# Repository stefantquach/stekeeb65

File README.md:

# stekeeb65

## Libraries
https://github.com/ai03-2725/MX_V2

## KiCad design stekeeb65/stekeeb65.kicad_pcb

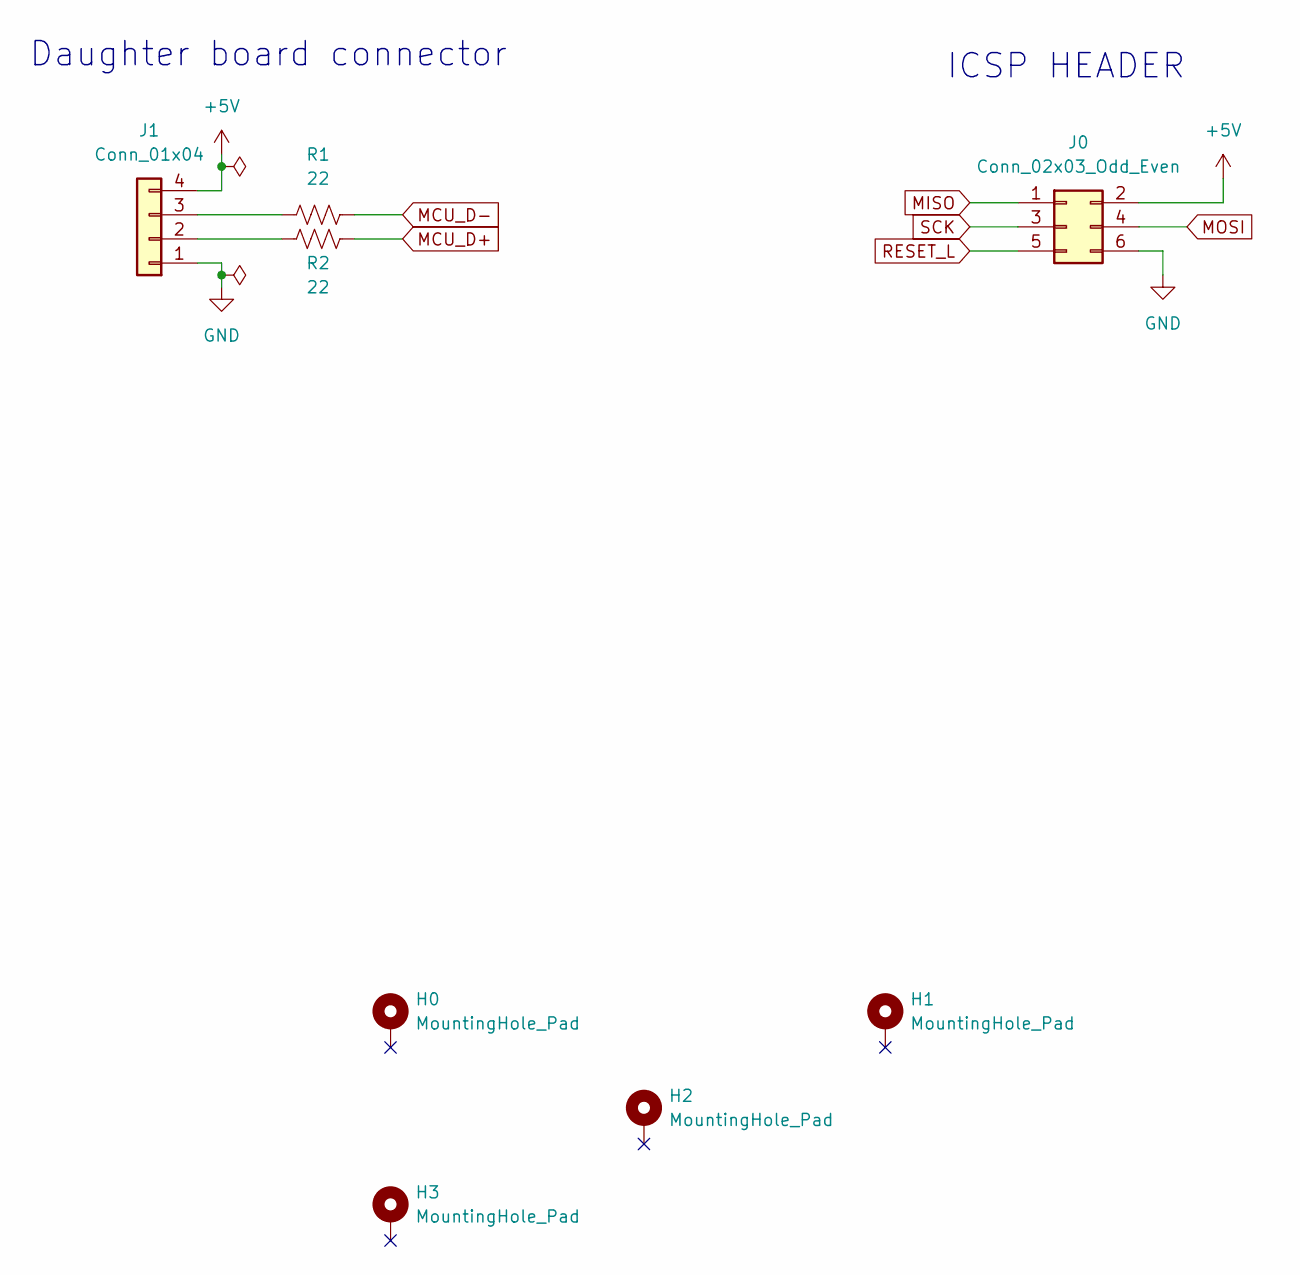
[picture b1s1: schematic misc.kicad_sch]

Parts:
H0, H1, H2, H3: MountingHole_Pad; MountingHole_2.2mm_M2_DIN965_Pad_TopBottom
J0: Conn_02x03_Odd_Even; PinHeader_2x03_P2.54mm_Vertical
J1: Conn_01x04; JST_SH_SM04B-SRSS-TB_1x04-1MP_P1.00mm_Horizontal
R1, R2: 22; R_0603_1608Metric_Pad0.98x0.95mm_HandSolder

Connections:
+5V: J0.2, J1.4; also elsewhere on the board
GND: J0.6, J1.1; also elsewhere on the board
MCU_D+: R2.1; also elsewhere on the board
MCU_D-: R1.2; also elsewhere on the board
MISO: J0.1; also elsewhere on the board
MOSI: J0.4; also elsewhere on the board
unnamed: J1.2, R2.2
unnamed: J1.3, R1.1
RESET_L: J0.5; also elsewhere on the board
SCK: J0.3; also elsewhere on the board

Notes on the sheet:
ICSP HEADER
Daughter board connector

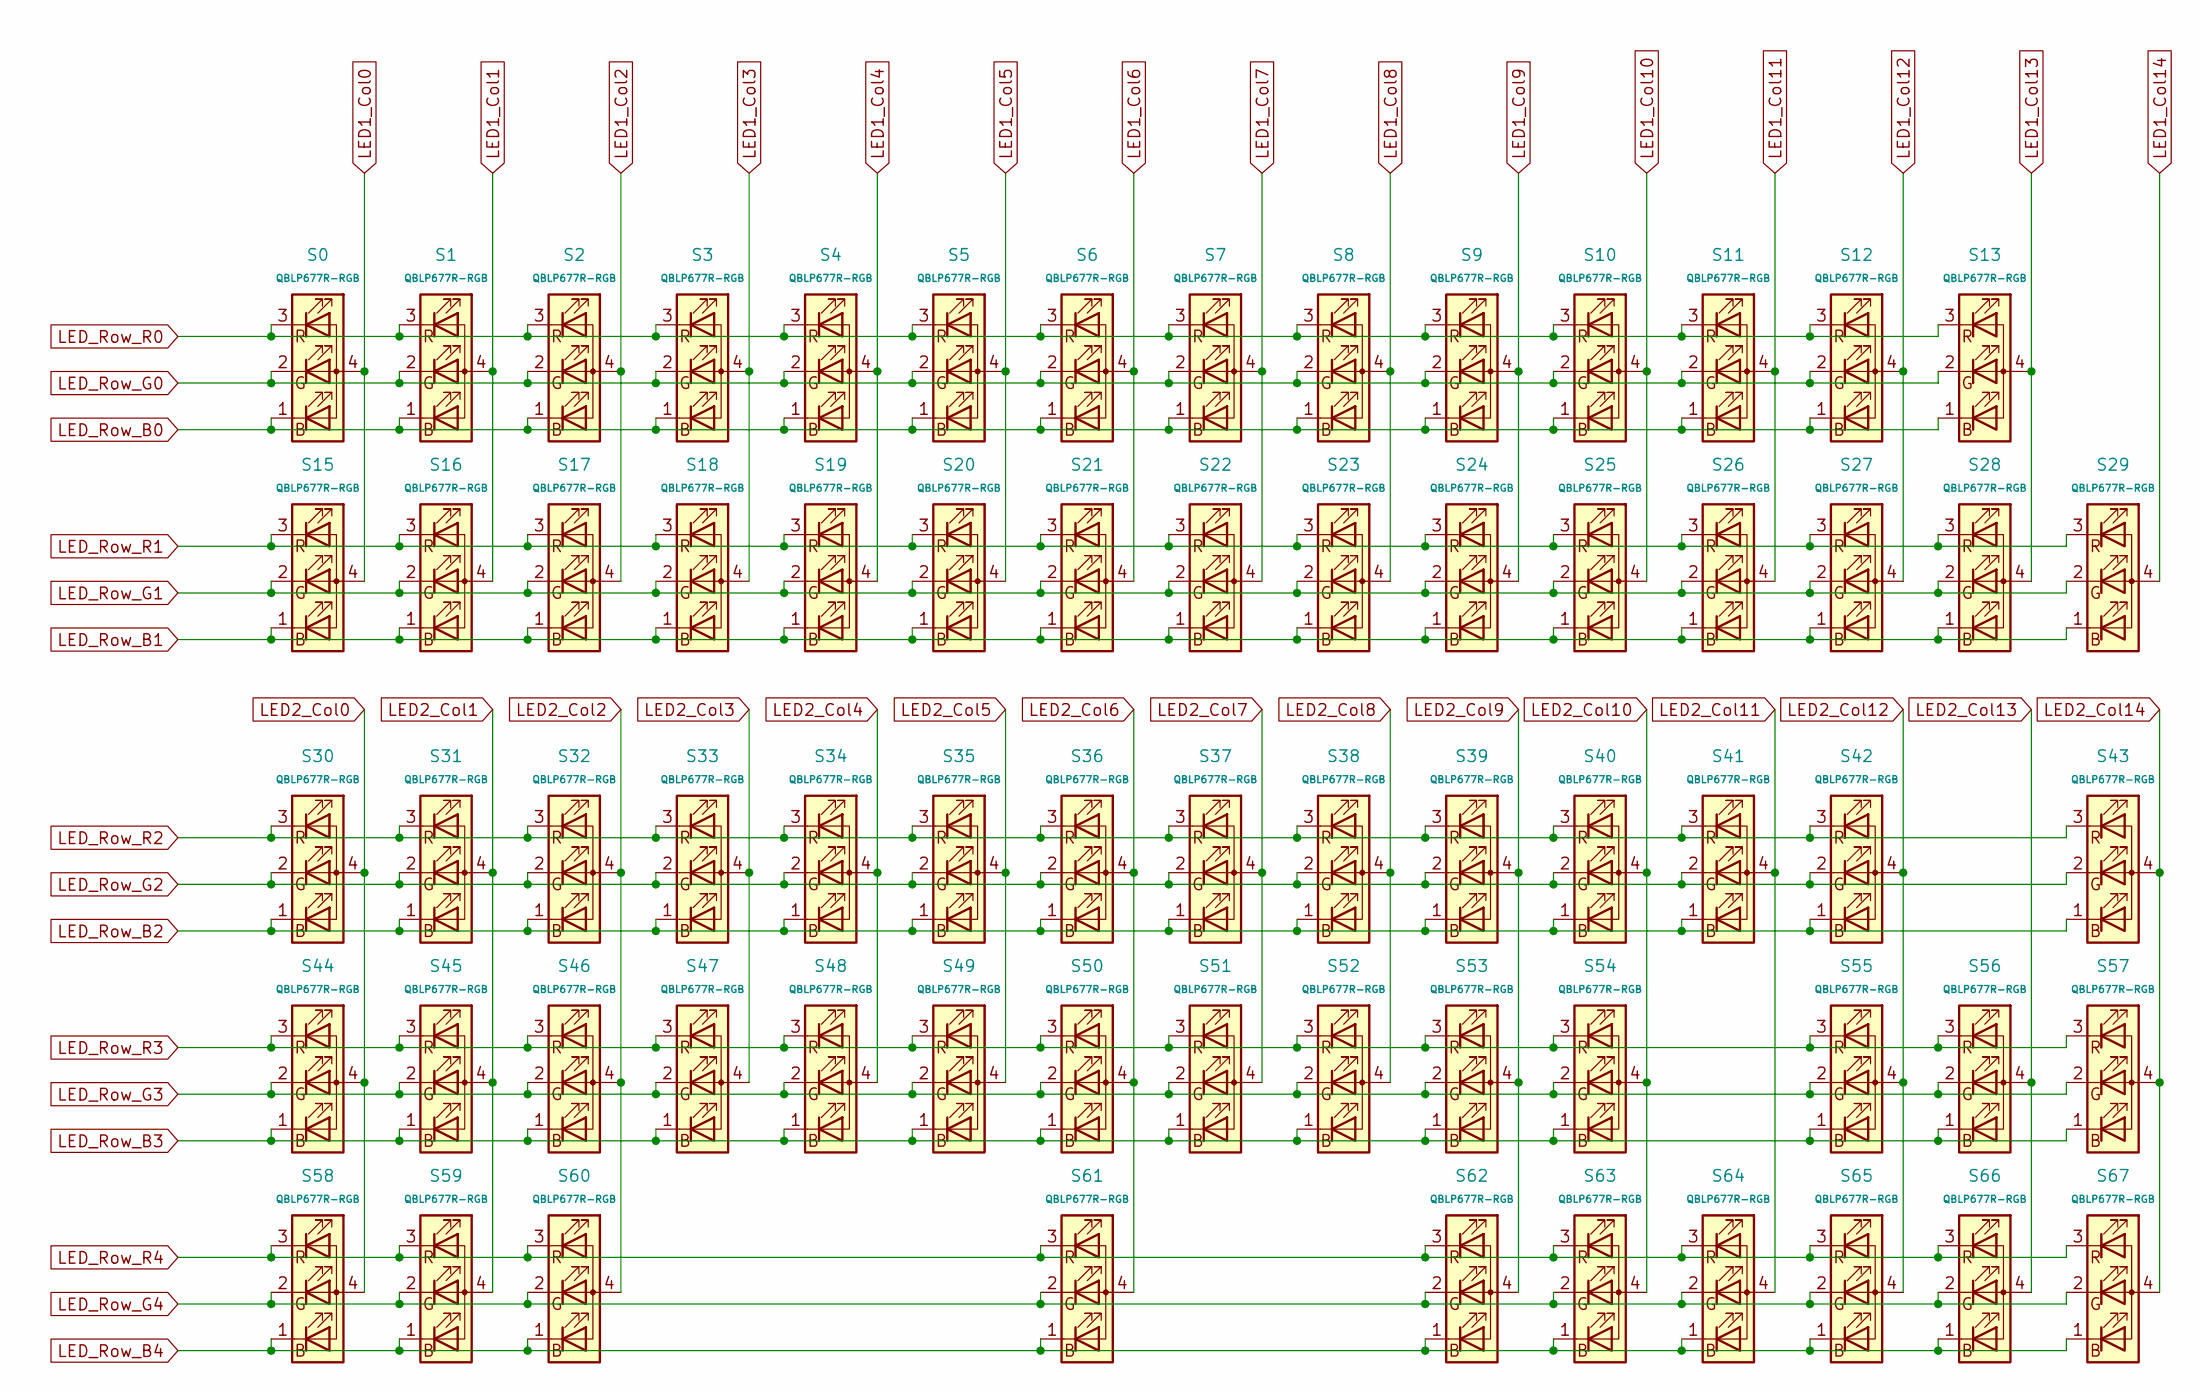
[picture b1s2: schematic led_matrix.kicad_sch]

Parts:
S0, S1, S2, S3, S4, S5, S6, S7, S8, S9, S10, S11, S12, S13, S15, S16, S17, S18, S19, S20, S21, S22, S23, S24, S25, S26, S27, S28, S29, S30, S31, S32, S33, S34, S35, S36, S37, S38, S39, S40, S41, S42, S43, S44, S45, S46, S47, S48, S49, S50, S51, S52, S53, S54, S55, S56, S57, S58, S59, S60, S61, S62, S63, S64, S65, S66, S67: QBLP677R-RGB; QBLP677R-RGB-square_cutout

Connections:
LED1_Col0: S0.4 (A), S15.4 (A); also elsewhere on the board
LED1_Col1: S1.4 (A), S16.4 (A); also elsewhere on the board
LED1_Col2: S2.4 (A), S17.4 (A); also elsewhere on the board
LED1_Col3: S3.4 (A), S18.4 (A); also elsewhere on the board
LED1_Col4: S4.4 (A), S19.4 (A); also elsewhere on the board
LED1_Col5: S5.4 (A), S20.4 (A); also elsewhere on the board
LED1_Col6: S6.4 (A), S21.4 (A); also elsewhere on the board
LED1_Col7: S7.4 (A), S22.4 (A); also elsewhere on the board
LED1_Col8: S8.4 (A), S23.4 (A); also elsewhere on the board
LED1_Col9: S9.4 (A), S24.4 (A); also elsewhere on the board
LED1_Col10: S10.4 (A), S25.4 (A); also elsewhere on the board
LED1_Col11: S11.4 (A), S26.4 (A); also elsewhere on the board
LED1_Col12: S12.4 (A), S27.4 (A); also elsewhere on the board
LED1_Col13: S13.4 (A), S28.4 (A); also elsewhere on the board
LED1_Col14: S29.4 (A); also elsewhere on the board
LED2_Col0: S30.4 (A), S44.4 (A), S58.4 (A); also elsewhere on the board
LED2_Col1: S31.4 (A), S45.4 (A), S59.4 (A); also elsewhere on the board
LED2_Col2: S32.4 (A), S46.4 (A), S60.4 (A); also elsewhere on the board
LED2_Col3: S33.4 (A), S47.4 (A); also elsewhere on the board
LED2_Col4: S34.4 (A), S48.4 (A); also elsewhere on the board
LED2_Col5: S35.4 (A), S49.4 (A); also elsewhere on the board
LED2_Col6: S36.4 (A), S50.4 (A), S61.4 (A); also elsewhere on the board
LED2_Col7: S37.4 (A), S51.4 (A); also elsewhere on the board
LED2_Col8: S38.4 (A), S52.4 (A); also elsewhere on the board
LED2_Col9: S39.4 (A), S53.4 (A), S62.4 (A); also elsewhere on the board
LED2_Col10: S40.4 (A), S54.4 (A), S63.4 (A); also elsewhere on the board
LED2_Col11: S41.4 (A), S64.4 (A); also elsewhere on the board
LED2_Col12: S42.4 (A), S55.4 (A), S65.4 (A); also elsewhere on the board
LED2_Col13: S56.4 (A), S66.4 (A); also elsewhere on the board
LED2_Col14: S43.4 (A), S57.4 (A), S67.4 (A); also elsewhere on the board
LED_Row_B0: S0.1 (BK), S1.1 (BK), S2.1 (BK), S3.1 (BK), S4.1 (BK), S5.1 (BK), S6.1 (BK), S7.1 (BK), S8.1 (BK), S9.1 (BK), S10.1 (BK), S11.1 (BK), S12.1 (BK), S13.1 (BK); also elsewhere on the board
LED_Row_B1: S15.1 (BK), S16.1 (BK), S17.1 (BK), S18.1 (BK), S19.1 (BK), S20.1 (BK), S21.1 (BK), S22.1 (BK), S23.1 (BK), S24.1 (BK), S25.1 (BK), S26.1 (BK), S27.1 (BK), S28.1 (BK), S29.1 (BK); also elsewhere on the board
LED_Row_B2: S30.1 (BK), S31.1 (BK), S32.1 (BK), S33.1 (BK), S34.1 (BK), S35.1 (BK), S36.1 (BK), S37.1 (BK), S38.1 (BK), S39.1 (BK), S40.1 (BK), S41.1 (BK), S42.1 (BK), S43.1 (BK); also elsewhere on the board
LED_Row_B3: S44.1 (BK), S45.1 (BK), S46.1 (BK), S47.1 (BK), S48.1 (BK), S49.1 (BK), S50.1 (BK), S51.1 (BK), S52.1 (BK), S53.1 (BK), S54.1 (BK), S55.1 (BK), S56.1 (BK), S57.1 (BK); also elsewhere on the board
LED_Row_B4: S58.1 (BK), S59.1 (BK), S60.1 (BK), S61.1 (BK), S62.1 (BK), S63.1 (BK), S64.1 (BK), S65.1 (BK), S66.1 (BK), S67.1 (BK); also elsewhere on the board
LED_Row_G0: S0.2 (GK), S1.2 (GK), S2.2 (GK), S3.2 (GK), S4.2 (GK), S5.2 (GK), S6.2 (GK), S7.2 (GK), S8.2 (GK), S9.2 (GK), S10.2 (GK), S11.2 (GK), S12.2 (GK), S13.2 (GK); also elsewhere on the board
LED_Row_G1: S15.2 (GK), S16.2 (GK), S17.2 (GK), S18.2 (GK), S19.2 (GK), S20.2 (GK), S21.2 (GK), S22.2 (GK), S23.2 (GK), S24.2 (GK), S25.2 (GK), S26.2 (GK), S27.2 (GK), S28.2 (GK), S29.2 (GK); also elsewhere on the board
LED_Row_G2: S30.2 (GK), S31.2 (GK), S32.2 (GK), S33.2 (GK), S34.2 (GK), S35.2 (GK), S36.2 (GK), S37.2 (GK), S38.2 (GK), S39.2 (GK), S40.2 (GK), S41.2 (GK), S42.2 (GK), S43.2 (GK); also elsewhere on the board
LED_Row_G3: S44.2 (GK), S45.2 (GK), S46.2 (GK), S47.2 (GK), S48.2 (GK), S49.2 (GK), S50.2 (GK), S51.2 (GK), S52.2 (GK), S53.2 (GK), S54.2 (GK), S55.2 (GK), S56.2 (GK), S57.2 (GK); also elsewhere on the board
LED_Row_G4: S58.2 (GK), S59.2 (GK), S60.2 (GK), S61.2 (GK), S62.2 (GK), S63.2 (GK), S64.2 (GK), S65.2 (GK), S66.2 (GK), S67.2 (GK); also elsewhere on the board
LED_Row_R0: S0.3 (RK), S1.3 (RK), S2.3 (RK), S3.3 (RK), S4.3 (RK), S5.3 (RK), S6.3 (RK), S7.3 (RK), S8.3 (RK), S9.3 (RK), S10.3 (RK), S11.3 (RK), S12.3 (RK), S13.3 (RK); also elsewhere on the board
LED_Row_R1: S15.3 (RK), S16.3 (RK), S17.3 (RK), S18.3 (RK), S19.3 (RK), S20.3 (RK), S21.3 (RK), S22.3 (RK), S23.3 (RK), S24.3 (RK), S25.3 (RK), S26.3 (RK), S27.3 (RK), S28.3 (RK), S29.3 (RK); also elsewhere on the board
LED_Row_R2: S30.3 (RK), S31.3 (RK), S32.3 (RK), S33.3 (RK), S34.3 (RK), S35.3 (RK), S36.3 (RK), S37.3 (RK), S38.3 (RK), S39.3 (RK), S40.3 (RK), S41.3 (RK), S42.3 (RK), S43.3 (RK); also elsewhere on the board
LED_Row_R3: S44.3 (RK), S45.3 (RK), S46.3 (RK), S47.3 (RK), S48.3 (RK), S49.3 (RK), S50.3 (RK), S51.3 (RK), S52.3 (RK), S53.3 (RK), S54.3 (RK), S55.3 (RK), S56.3 (RK), S57.3 (RK); also elsewhere on the board
LED_Row_R4: S58.3 (RK), S59.3 (RK), S60.3 (RK), S61.3 (RK), S62.3 (RK), S63.3 (RK), S64.3 (RK), S65.3 (RK), S66.3 (RK), S67.3 (RK); also elsewhere on the board

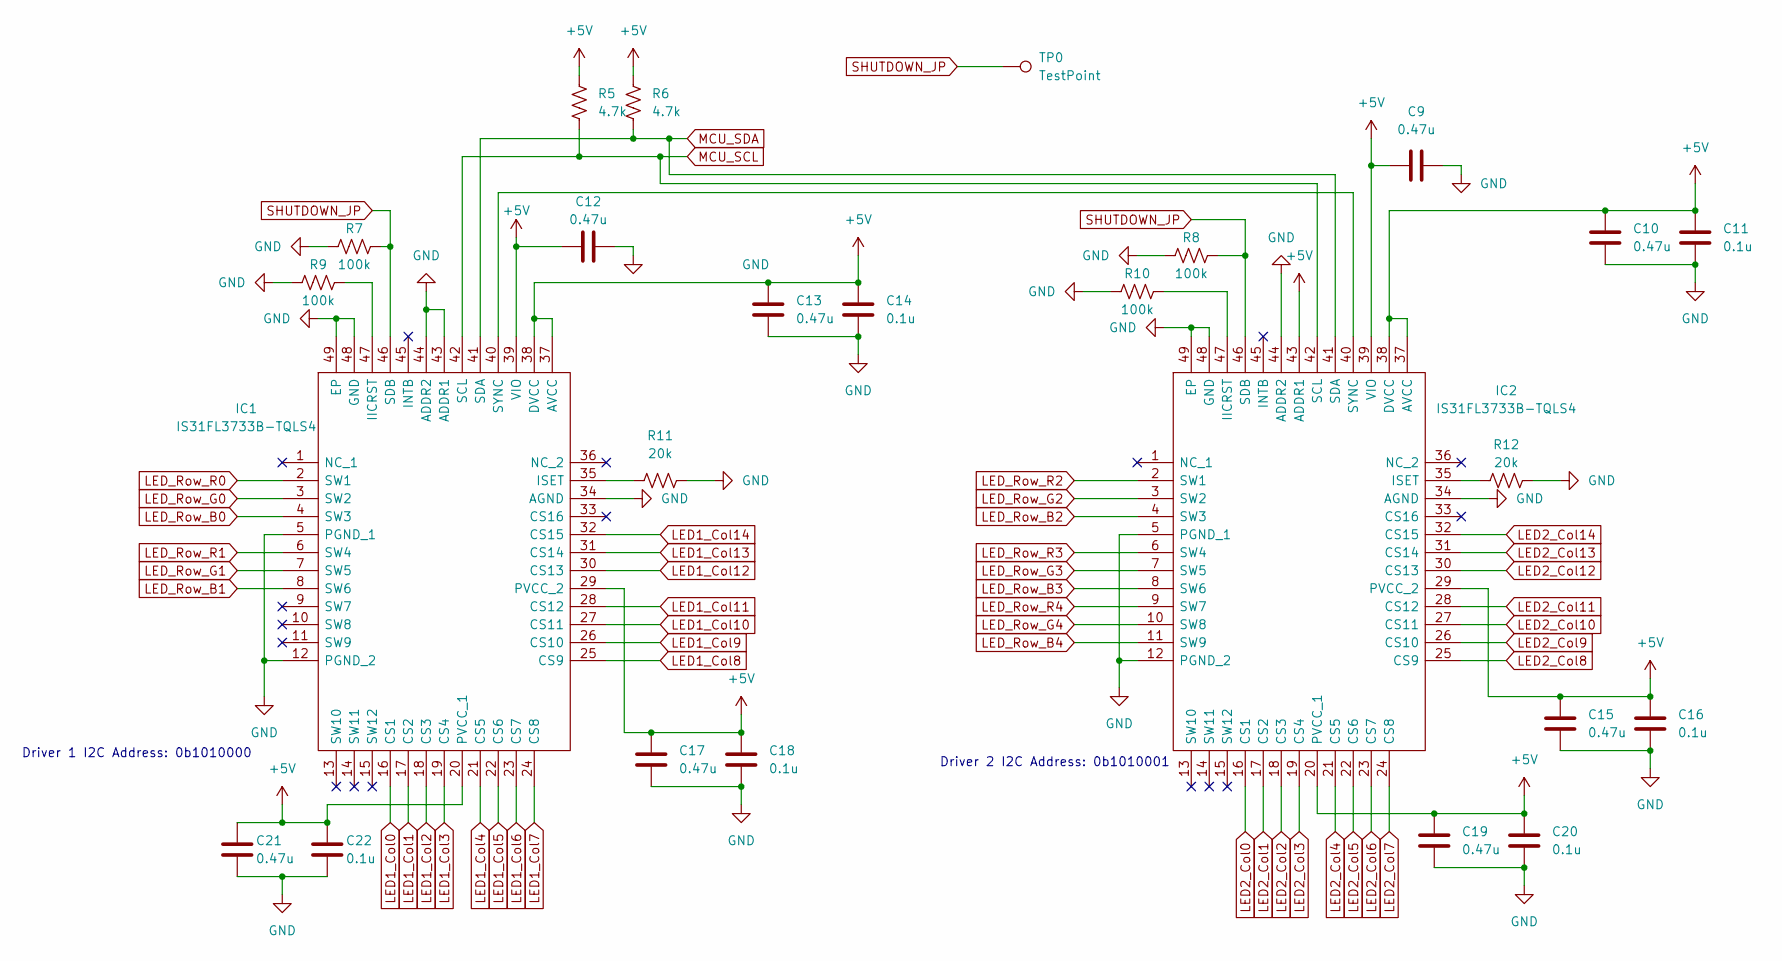
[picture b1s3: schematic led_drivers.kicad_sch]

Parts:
C9, C10, C12, C13, C15, C17, C19, C21: 0.47u; C_0603_1608Metric_Pad1.08x0.95mm_HandSolder
C11, C14, C16, C18, C20, C22: 0.1u; C_0603_1608Metric_Pad1.08x0.95mm_HandSolder
IC1, IC2: IS31FL3733B-TQLS4; QFP50P900X900X120-49N; Manufacturer_Part_Number IS31FL3733B-TQLS4; Mouser Part Number 870-IS313733B-TQLS4
R5, R6: 4.7k; R_0603_1608Metric_Pad0.98x0.95mm_HandSolder
R7, R8, R9, R10: 100k; R_0603_1608Metric_Pad0.98x0.95mm_HandSolder
R11, R12: 20k; R_0603_1608Metric_Pad0.98x0.95mm_HandSolder
TP0: TestPoint; TestPoint_Pad_D1.0mm

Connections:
+5V: C9.1, C10.1, C11.1, C12.1, C13.1, C14.1, C15.1, C16.1, C17.1, C18.1, C19.1, C20.1, C21.1, C22.1, IC1.20 (PVCC_1), IC1.29 (PVCC_2), IC1.37 (AVCC), IC1.38 (DVCC), IC1.39 (VIO), IC2.20 (PVCC_1), IC2.29 (PVCC_2), IC2.37 (AVCC), IC2.38 (DVCC), IC2.39 (VIO), IC2.43 (ADDR1), R5.1, R6.1; also elsewhere on the board
GND: C9.2, C10.2, C11.2, C12.2, C13.2, C14.2, C15.2, C16.2, C17.2, C18.2, C19.2, C20.2, C21.2, C22.2, IC1.5 (PGND_1), IC1.12 (PGND_2), IC1.34 (AGND), IC1.43 (ADDR1), IC1.44 (ADDR2), IC1.48 (GND), IC1.49 (EP), IC2.5 (PGND_1), IC2.12 (PGND_2), IC2.34 (AGND), IC2.44 (ADDR2), IC2.48 (GND), IC2.49 (EP), R7.1, R8.1, R9.1, R10.1, R11.2, R12.2; also elsewhere on the board
LED1_Col0: IC1.16 (CS1); also elsewhere on the board
LED1_Col1: IC1.17 (CS2); also elsewhere on the board
LED1_Col2: IC1.18 (CS3); also elsewhere on the board
LED1_Col3: IC1.19 (CS4); also elsewhere on the board
LED1_Col4: IC1.21 (CS5); also elsewhere on the board
LED1_Col5: IC1.22 (CS6); also elsewhere on the board
LED1_Col6: IC1.23 (CS7); also elsewhere on the board
LED1_Col7: IC1.24 (CS8); also elsewhere on the board
LED1_Col8: IC1.25 (CS9); also elsewhere on the board
LED1_Col9: IC1.26 (CS10); also elsewhere on the board
LED1_Col10: IC1.27 (CS11); also elsewhere on the board
LED1_Col11: IC1.28 (CS12); also elsewhere on the board
LED1_Col12: IC1.30 (CS13); also elsewhere on the board
LED1_Col13: IC1.31 (CS14); also elsewhere on the board
LED1_Col14: IC1.32 (CS15); also elsewhere on the board
LED2_Col0: IC2.16 (CS1); also elsewhere on the board
LED2_Col1: IC2.17 (CS2); also elsewhere on the board
LED2_Col2: IC2.18 (CS3); also elsewhere on the board
LED2_Col3: IC2.19 (CS4); also elsewhere on the board
LED2_Col4: IC2.21 (CS5); also elsewhere on the board
LED2_Col5: IC2.22 (CS6); also elsewhere on the board
LED2_Col6: IC2.23 (CS7); also elsewhere on the board
LED2_Col7: IC2.24 (CS8); also elsewhere on the board
LED2_Col8: IC2.25 (CS9); also elsewhere on the board
LED2_Col9: IC2.26 (CS10); also elsewhere on the board
LED2_Col10: IC2.27 (CS11); also elsewhere on the board
LED2_Col11: IC2.28 (CS12); also elsewhere on the board
LED2_Col12: IC2.30 (CS13); also elsewhere on the board
LED2_Col13: IC2.31 (CS14); also elsewhere on the board
LED2_Col14: IC2.32 (CS15); also elsewhere on the board
LED_Row_B0: IC1.4 (SW3); also elsewhere on the board
LED_Row_B1: IC1.8 (SW6); also elsewhere on the board
LED_Row_B2: IC2.4 (SW3); also elsewhere on the board
LED_Row_B3: IC2.8 (SW6); also elsewhere on the board
LED_Row_B4: IC2.11 (SW9); also elsewhere on the board
LED_Row_G0: IC1.3 (SW2); also elsewhere on the board
LED_Row_G1: IC1.7 (SW5); also elsewhere on the board
LED_Row_G2: IC2.3 (SW2); also elsewhere on the board
LED_Row_G3: IC2.7 (SW5); also elsewhere on the board
LED_Row_G4: IC2.10 (SW8); also elsewhere on the board
LED_Row_R0: IC1.2 (SW1); also elsewhere on the board
LED_Row_R1: IC1.6 (SW4); also elsewhere on the board
LED_Row_R2: IC2.2 (SW1); also elsewhere on the board
LED_Row_R3: IC2.6 (SW4); also elsewhere on the board
LED_Row_R4: IC2.9 (SW7); also elsewhere on the board
MCU_SCL: IC1.42 (SCL), IC2.42 (SCL), R5.2; also elsewhere on the board
MCU_SDA: IC1.41 (SDA), IC2.41 (SDA), R6.2; also elsewhere on the board
unnamed: IC1.35 (ISET), R11.1
unnamed: IC1.40 (SYNC), IC2.40 (SYNC)
unnamed: IC1.47 (IICRST), R9.2
unnamed: IC2.35 (ISET), R12.1
unnamed: IC2.47 (IICRST), R10.2
SHUTDOWN_JP: IC1.46 (SDB), IC2.46 (SDB), R7.2, R8.2, TP0.1

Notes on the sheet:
Driver 1 I2C Address: 0b1010000
Driver 2 I2C Address: 0b1010001

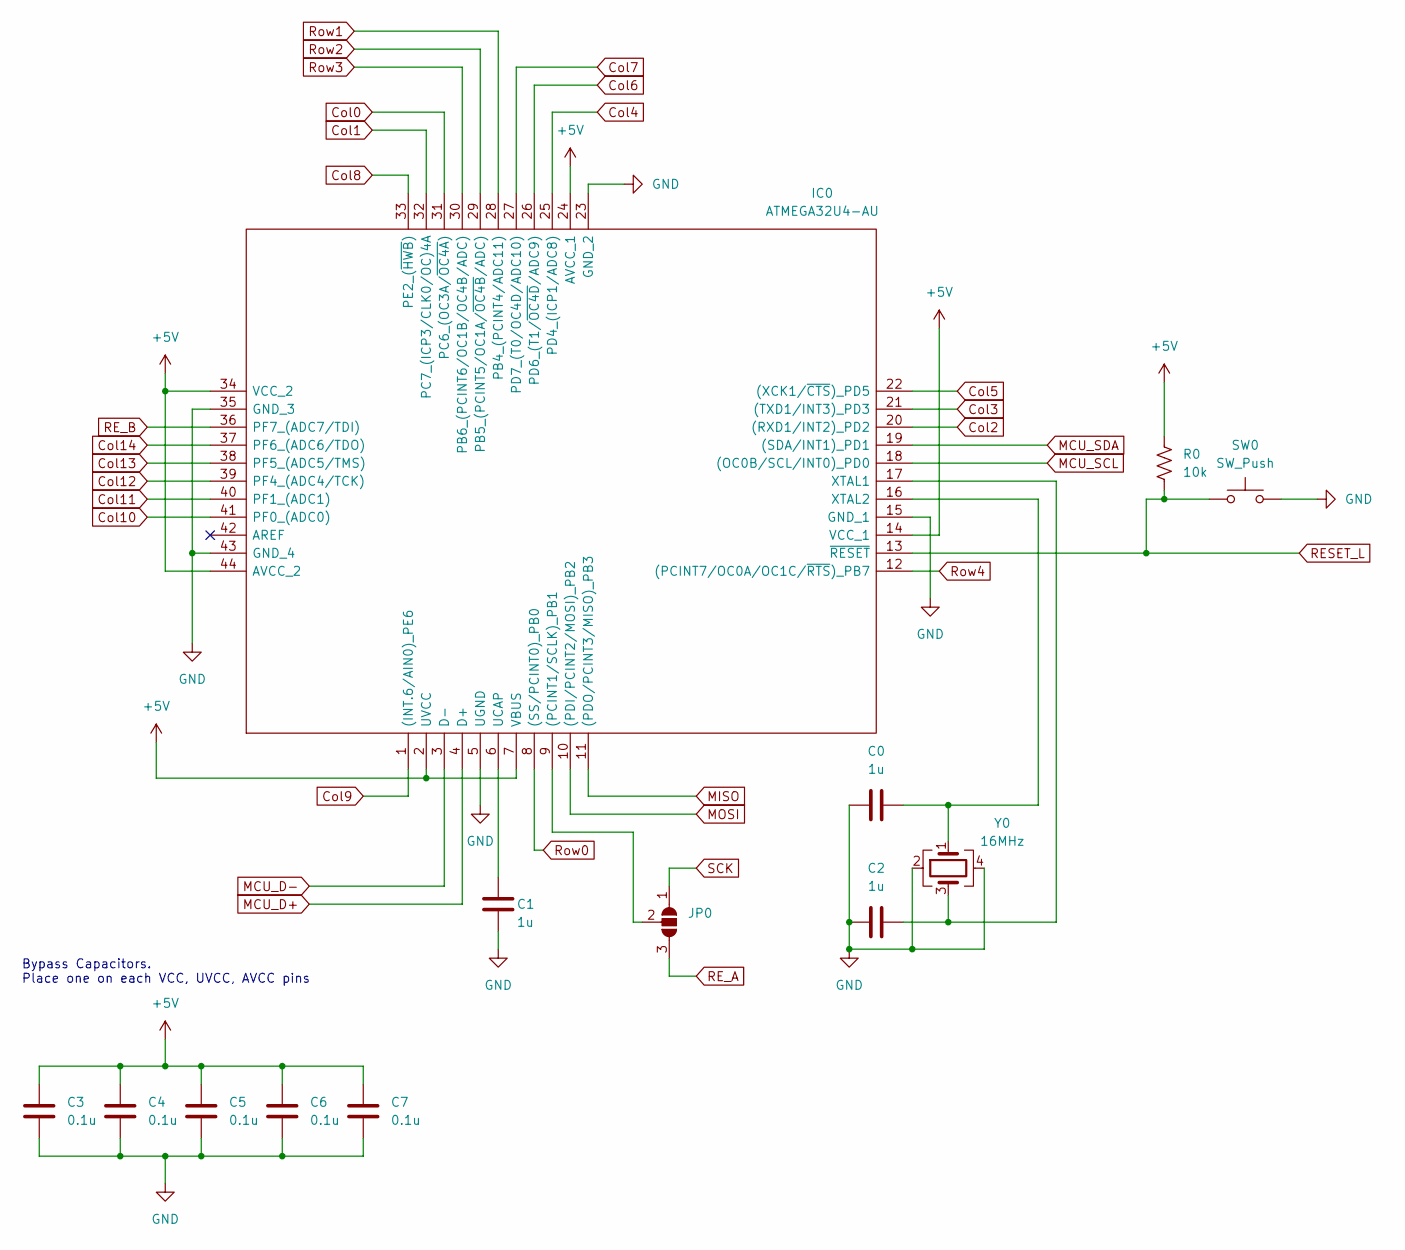
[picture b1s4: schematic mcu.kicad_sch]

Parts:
C0, C1, C2: 1u; C_0603_1608Metric_Pad1.08x0.95mm_HandSolder
C3, C4, C5, C6, C7: 0.1u; C_0603_1608Metric_Pad1.08x0.95mm_HandSolder
IC0: ATMEGA32U4-AU; QFP80P1200X1200X120-44N; Manufacturer_Part_Number ATMEGA32U4-AU; Mouser Part Number 556-ATMEGA32U4-AU
JP0: SolderJumper_3_Open; SolderJumper-3_P1.3mm_Open_RoundedPad1.0x1.5mm
R0: 10k; R_0603_1608Metric_Pad0.98x0.95mm_HandSolder
SW0: SW_Push; RS187R05A2DSMTRT
Y0: 16MHz; Crystal_SMD_3225-4Pin_3.2x2.5mm

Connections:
+5V: C3.1, C4.1, C5.1, C6.1, C7.1, IC0.2 (UVCC), IC0.7 (VBUS), IC0.14 (VCC_1), IC0.24 (AVCC_1), IC0.34 (VCC_2), IC0.44 (AVCC_2), R0.2; also elsewhere on the board
Col0: IC0.31 (PC6_(OC3A/~OC4A)); also elsewhere on the board
Col1: IC0.32 (PC7_(ICP3/CLK0/OC)4A); also elsewhere on the board
Col2: IC0.20 ((RXD1/INT2)_PD2); also elsewhere on the board
Col3: IC0.21 ((TXD1/INT3)_PD3); also elsewhere on the board
Col4: IC0.25 (PD4_(ICP1/ADC8)); also elsewhere on the board
Col5: IC0.22 ((XCK1/~CTS)_PD5); also elsewhere on the board
Col6: IC0.26 (PD6_(T1/~OC4D/ADC9)); also elsewhere on the board
Col7: IC0.27 (PD7_(T0/OC4D/ADC10)); also elsewhere on the board
Col8: IC0.33 (PE2_(~HWB)); also elsewhere on the board
Col9: IC0.1 ((INT.6/AIN0)_PE6); also elsewhere on the board
Col10: IC0.41 (PF0_(ADC0)); also elsewhere on the board
Col11: IC0.40 (PF1_(ADC1)); also elsewhere on the board
Col12: IC0.39 (PF4_(ADC4/TCK)); also elsewhere on the board
Col13: IC0.38 (PF5_(ADC5/TMS)); also elsewhere on the board
Col14: IC0.37 (PF6_(ADC6/TDO)); also elsewhere on the board
GND: C0.2, C1.2, C2.2, C3.2, C4.2, C5.2, C6.2, C7.2, IC0.5 (UGND), IC0.15 (GND_1), IC0.23 (GND_2), IC0.35 (GND_3), IC0.43 (GND_4), SW0.2, Y0.2, Y0.4; also elsewhere on the board
MCU_D+: IC0.4 (D+); also elsewhere on the board
MCU_D-: IC0.3 (D-); also elsewhere on the board
MCU_SCL: IC0.18 ((OC0B/SCL/INT0)_PD0); also elsewhere on the board
MCU_SDA: IC0.19 ((SDA/INT1)_PD1); also elsewhere on the board
MISO: IC0.11 ((PDO/PCINT3/MISO)_PB3); also elsewhere on the board
MOSI: IC0.10 ((PDI/PCINT2/MOSI)_PB2); also elsewhere on the board
unnamed: C0.1, IC0.16 (XTAL2), Y0.1
unnamed: C1.1, IC0.6 (UCAP)
unnamed: C2.1, IC0.17 (XTAL1), Y0.3
unnamed: IC0.9 ((PCINT1/SCLK)_PB1), JP0.2 (C)
RESET_L: IC0.13 (~RESET), R0.1, SW0.1; also elsewhere on the board
RE_A: JP0.3 (B); also elsewhere on the board
RE_B: IC0.36 (PF7_(ADC7/TDI)); also elsewhere on the board
Row0: IC0.8 ((SS/PCINT0)_PB0); also elsewhere on the board
Row1: IC0.28 (PB4_(PCINT4/ADC11)); also elsewhere on the board
Row2: IC0.29 (PB5_(PCINT5/OC1A/~OC4B/ADC)); also elsewhere on the board
Row3: IC0.30 (PB6_(PCINT6/OC1B/OC4B/ADC)); also elsewhere on the board
Row4: IC0.12 ((PCINT7/OC0A/OC1C/~RTS)_PB7); also elsewhere on the board
SCK: JP0.1 (A); also elsewhere on the board

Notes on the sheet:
Bypass Capacitors. Place one on each VCC, UVCC, AVCC pins

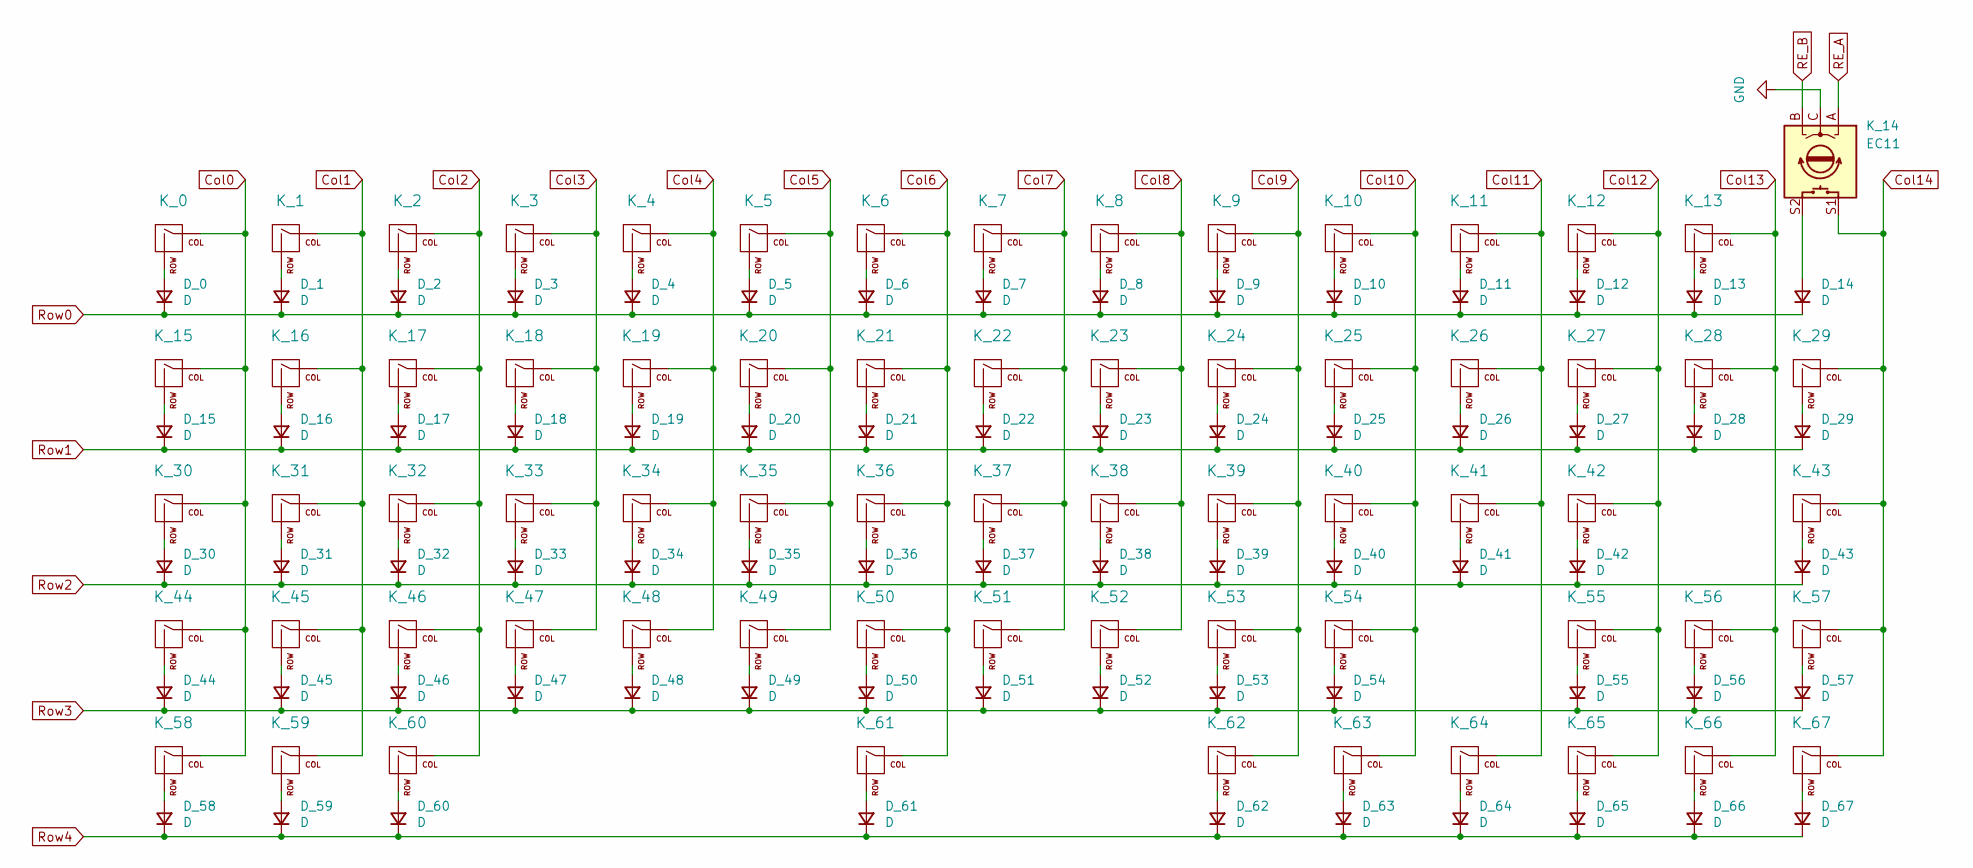
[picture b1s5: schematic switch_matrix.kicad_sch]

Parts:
D_0, D_1, D_2, D_3, D_4, D_5, D_6, D_7, D_8, D_9, D_10, D_11, D_12, D_13, D_14, D_15, D_16, D_17, D_18, D_19, D_20, D_21, D_22, D_23, D_24, D_25, D_26, D_27, D_28, D_29, D_30, D_31, D_32, D_33, D_34, D_35, D_36, D_37, D_38, D_39, D_40, D_41, D_42, D_43, D_44, D_45, D_46, D_47, D_48, D_49, D_50, D_51, D_52, D_53, D_54, D_55, D_56, D_57, D_58, D_59, D_60, D_61, D_62, D_63, D_64, D_65, D_66, D_67: D; D_SOD-123-Pretty
K_0, K_1, K_2, K_3, K_4, K_5, K_6, K_7, K_8, K_9, K_10, K_11, K_12, K_16, K_17, K_18, K_19, K_20, K_21, K_22, K_23, K_24, K_25, K_26, K_27, K_29, K_31, K_32, K_33, K_34, K_35, K_36, K_37, K_38, K_39, K_40, K_41, K_43, K_45, K_46, K_47, K_48, K_49, K_50, K_51, K_52, K_53, K_54, K_56, K_57, K_62, K_63, K_64, K_65, K_66, K_67: KEYSW; MX-Hotswap-1U
K_13: KEYSW; MX-Hotswap-2U
K_14: EC11; RotaryEncoder_Alps_EC11E-Switch-Vertical-EDIT
K_15, K_28: KEYSW; MX-Hotswap-1.5U
K_30, K_55: KEYSW; MX-Hotswap-1.75U
K_42, K_44: KEYSW; MX-Hotswap-2.25U
K_58, K_59, K_60: KEYSW; MX-Hotswap-1.25U
K_61: KEYSW; MX-Hotswap-6.25U-ReversedStabilizers

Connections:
Col0: K_0.1 (COL), K_15.1 (COL), K_30.1 (COL), K_44.1 (COL), K_58.1 (COL); also elsewhere on the board
Col1: K_1.1 (COL), K_16.1 (COL), K_31.1 (COL), K_45.1 (COL), K_59.1 (COL); also elsewhere on the board
Col2: K_2.1 (COL), K_17.1 (COL), K_32.1 (COL), K_46.1 (COL), K_60.1 (COL); also elsewhere on the board
Col3: K_3.1 (COL), K_18.1 (COL), K_33.1 (COL), K_47.1 (COL); also elsewhere on the board
Col4: K_4.1 (COL), K_19.1 (COL), K_34.1 (COL), K_48.1 (COL); also elsewhere on the board
Col5: K_5.1 (COL), K_20.1 (COL), K_35.1 (COL), K_49.1 (COL); also elsewhere on the board
Col6: K_6.1 (COL), K_21.1 (COL), K_36.1 (COL), K_50.1 (COL), K_61.1 (COL); also elsewhere on the board
Col7: K_7.1 (COL), K_22.1 (COL), K_37.1 (COL), K_51.1 (COL); also elsewhere on the board
Col8: K_8.1 (COL), K_23.1 (COL), K_38.1 (COL), K_52.1 (COL); also elsewhere on the board
Col9: K_9.1 (COL), K_24.1 (COL), K_39.1 (COL), K_53.1 (COL), K_62.1 (COL); also elsewhere on the board
Col10: K_10.1 (COL), K_25.1 (COL), K_40.1 (COL), K_54.1 (COL), K_63.1 (COL); also elsewhere on the board
Col11: K_11.1 (COL), K_26.1 (COL), K_41.1 (COL), K_64.1 (COL); also elsewhere on the board
Col12: K_12.1 (COL), K_27.1 (COL), K_42.1 (COL), K_55.1 (COL), K_65.1 (COL); also elsewhere on the board
Col13: K_13.1 (COL), K_28.1 (COL), K_56.1 (COL), K_66.1 (COL); also elsewhere on the board
Col14: K_14.S1, K_29.1 (COL), K_43.1 (COL), K_57.1 (COL), K_67.1 (COL); also elsewhere on the board
GND: K_14.C; also elsewhere on the board
unnamed: D_0.2 (A), K_0.2 (ROW)
unnamed: D_1.2 (A), K_1.2 (ROW)
unnamed: D_2.2 (A), K_2.2 (ROW)
unnamed: D_3.2 (A), K_3.2 (ROW)
unnamed: D_4.2 (A), K_4.2 (ROW)
unnamed: D_5.2 (A), K_5.2 (ROW)
unnamed: D_6.2 (A), K_6.2 (ROW)
unnamed: D_7.2 (A), K_7.2 (ROW)
unnamed: D_8.2 (A), K_8.2 (ROW)
unnamed: D_9.2 (A), K_9.2 (ROW)
unnamed: D_10.2 (A), K_10.2 (ROW)
unnamed: D_11.2 (A), K_11.2 (ROW)
unnamed: D_12.2 (A), K_12.2 (ROW)
unnamed: D_13.2 (A), K_13.2 (ROW)
unnamed: D_14.2 (A), K_14.S2
unnamed: D_15.2 (A), K_15.2 (ROW)
unnamed: D_16.2 (A), K_16.2 (ROW)
unnamed: D_17.2 (A), K_17.2 (ROW)
unnamed: D_18.2 (A), K_18.2 (ROW)
unnamed: D_19.2 (A), K_19.2 (ROW)
unnamed: D_20.2 (A), K_20.2 (ROW)
unnamed: D_21.2 (A), K_21.2 (ROW)
unnamed: D_22.2 (A), K_22.2 (ROW)
unnamed: D_23.2 (A), K_23.2 (ROW)
unnamed: D_24.2 (A), K_24.2 (ROW)
unnamed: D_25.2 (A), K_25.2 (ROW)
unnamed: D_26.2 (A), K_26.2 (ROW)
unnamed: D_27.2 (A), K_27.2 (ROW)
unnamed: D_28.2 (A), K_28.2 (ROW)
unnamed: D_29.2 (A), K_29.2 (ROW)
unnamed: D_30.2 (A), K_30.2 (ROW)
unnamed: D_31.2 (A), K_31.2 (ROW)
unnamed: D_32.2 (A), K_32.2 (ROW)
unnamed: D_33.2 (A), K_33.2 (ROW)
unnamed: D_34.2 (A), K_34.2 (ROW)
unnamed: D_35.2 (A), K_35.2 (ROW)
unnamed: D_36.2 (A), K_36.2 (ROW)
unnamed: D_37.2 (A), K_37.2 (ROW)
unnamed: D_38.2 (A), K_38.2 (ROW)
unnamed: D_39.2 (A), K_39.2 (ROW)
unnamed: D_40.2 (A), K_40.2 (ROW)
unnamed: D_41.2 (A), K_41.2 (ROW)
unnamed: D_42.2 (A), K_42.2 (ROW)
unnamed: D_43.2 (A), K_43.2 (ROW)
unnamed: D_44.2 (A), K_44.2 (ROW)
unnamed: D_45.2 (A), K_45.2 (ROW)
unnamed: D_46.2 (A), K_46.2 (ROW)
unnamed: D_47.2 (A), K_47.2 (ROW)
unnamed: D_48.2 (A), K_48.2 (ROW)
unnamed: D_49.2 (A), K_49.2 (ROW)
unnamed: D_50.2 (A), K_50.2 (ROW)
unnamed: D_51.2 (A), K_51.2 (ROW)
unnamed: D_52.2 (A), K_52.2 (ROW)
unnamed: D_53.2 (A), K_53.2 (ROW)
unnamed: D_54.2 (A), K_54.2 (ROW)
unnamed: D_55.2 (A), K_55.2 (ROW)
unnamed: D_56.2 (A), K_56.2 (ROW)
unnamed: D_57.2 (A), K_57.2 (ROW)
unnamed: D_58.2 (A), K_58.2 (ROW)
unnamed: D_59.2 (A), K_59.2 (ROW)
unnamed: D_60.2 (A), K_60.2 (ROW)
unnamed: D_61.2 (A), K_61.2 (ROW)
unnamed: D_62.2 (A), K_62.2 (ROW)
unnamed: D_63.2 (A), K_63.2 (ROW)
unnamed: D_64.2 (A), K_64.2 (ROW)
unnamed: D_65.2 (A), K_65.2 (ROW)
unnamed: D_66.2 (A), K_66.2 (ROW)
unnamed: D_67.2 (A), K_67.2 (ROW)
RE_A: K_14.A; also elsewhere on the board
RE_B: K_14.B; also elsewhere on the board
Row0: D_0.1 (K), D_1.1 (K), D_2.1 (K), D_3.1 (K), D_4.1 (K), D_5.1 (K), D_6.1 (K), D_7.1 (K), D_8.1 (K), D_9.1 (K), D_10.1 (K), D_11.1 (K), D_12.1 (K), D_13.1 (K), D_14.1 (K); also elsewhere on the board
Row1: D_15.1 (K), D_16.1 (K), D_17.1 (K), D_18.1 (K), D_19.1 (K), D_20.1 (K), D_21.1 (K), D_22.1 (K), D_23.1 (K), D_24.1 (K), D_25.1 (K), D_26.1 (K), D_27.1 (K), D_28.1 (K), D_29.1 (K); also elsewhere on the board
Row2: D_30.1 (K), D_31.1 (K), D_32.1 (K), D_33.1 (K), D_34.1 (K), D_35.1 (K), D_36.1 (K), D_37.1 (K), D_38.1 (K), D_39.1 (K), D_40.1 (K), D_41.1 (K), D_42.1 (K), D_43.1 (K); also elsewhere on the board
Row3: D_44.1 (K), D_45.1 (K), D_46.1 (K), D_47.1 (K), D_48.1 (K), D_49.1 (K), D_50.1 (K), D_51.1 (K), D_52.1 (K), D_53.1 (K), D_54.1 (K), D_55.1 (K), D_56.1 (K), D_57.1 (K); also elsewhere on the board
Row4: D_58.1 (K), D_59.1 (K), D_60.1 (K), D_61.1 (K), D_62.1 (K), D_63.1 (K), D_64.1 (K), D_65.1 (K), D_66.1 (K), D_67.1 (K); also elsewhere on the board

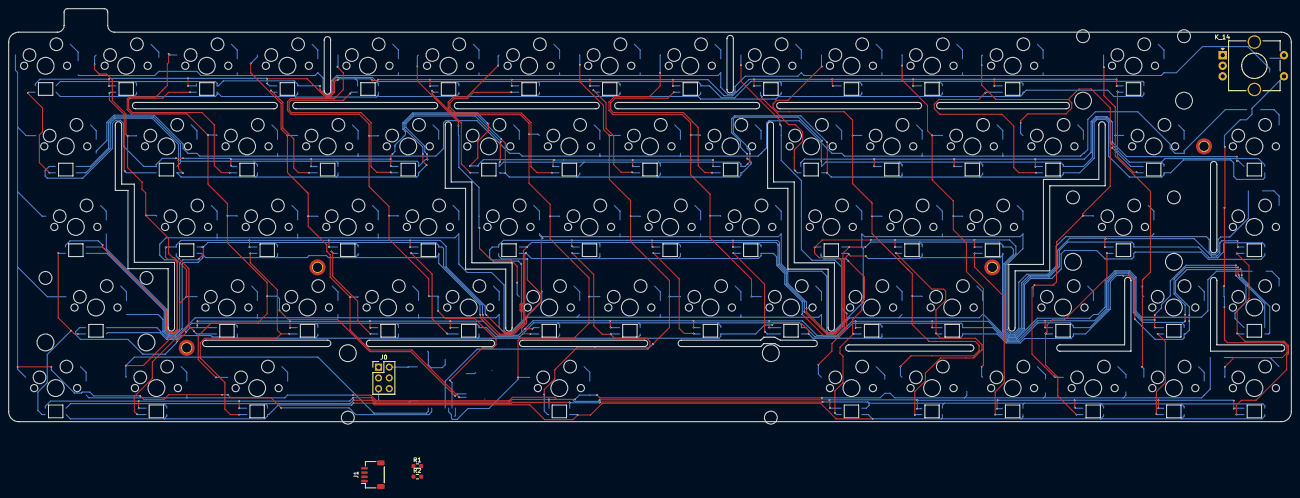
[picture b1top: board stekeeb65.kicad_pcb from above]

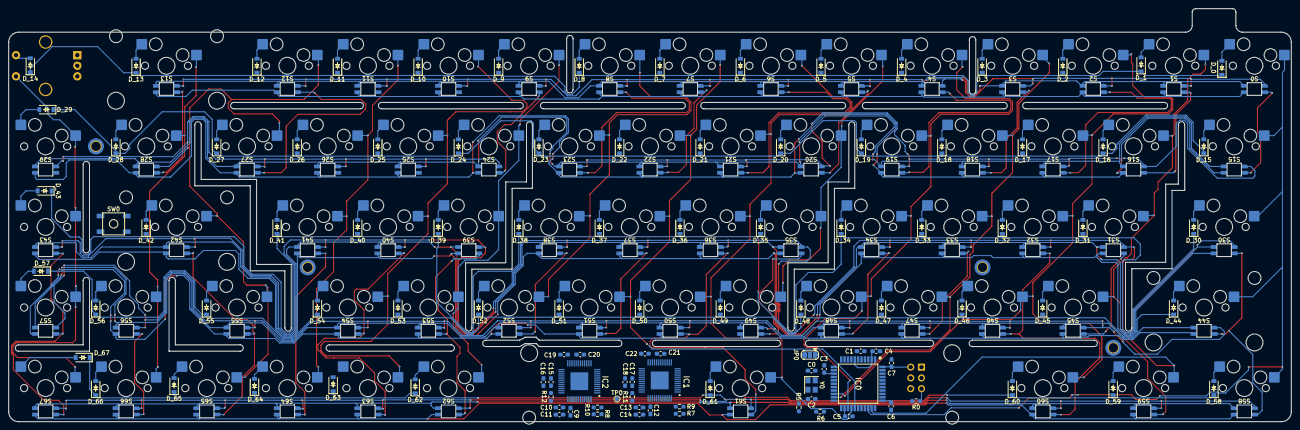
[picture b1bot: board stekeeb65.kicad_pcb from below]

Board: 2 copper layers, 303.2 x 97.6 mm, 249 parts (173 on the bottom side), 157 nets.

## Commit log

2022-11-06 Initial commit of schematic
2022-11-06 cleaning up
2022-11-11 Adding keyboard footprints
2022-11-18 Committing before changes to PCB
2022-11-18 updating script
2022-11-18 Adding key layout with leds
2022-11-19 Adding layout for diodes, LEDs, edge cuts
2022-11-20 Started layout for keyboard. still need to verify LED driver schematic
2022-11-21 Redoing keyboard layout. Adding flex cuts to PCB
2022-11-26 Finish routing matrix
2022-12-04 Replacing Type-C in lieu of a daughter board connector.
2023-01-21 Interim commit before potentially breaking stuff
